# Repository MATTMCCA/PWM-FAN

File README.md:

# PWM-FAN Controller

25Khz PWM fan controller for fume extractor. Duty Range: 5%-95%, requires an external 12v supply.

Designed to control Dell Server Grade cooling fan's (*because I have one already*), or any 4-wire PC case fan.

[4-wire Fan](https://www.digikey.com/short/5pwf955c)

[Another Fan](https://www.newegg.com/p/1YF-00B0-00V81)

[Overkill Fan **2Amps**](https://www.amazon.com/Wathai-5300rpm-Airflow-Brushless-Cooling/dp/B07SGWNV5J)

## Parts-List
[DigiCart](https://www.digikey.com/short/1bbnzr3q)

___
## Notes

Some ```things``` that have caused concern are as follows,

- The Datasheet states the min/max rpm of the fan during pwm operation, ```0 rpm - 4800 rpm```. However, it also implies that the fan will never reach 0 rpm. So what exactly is the minimum speed achievable?
- I didn't add a power switch or pads for an off-board switch :rage1: . Guess ill just unplug it when I want it off? or wire a switch in series with the fan +12v wire? (**which should be rated for 2A**).
- Why do all fan controllers on amazon use high side switching instead of the actual pwm control cooked into the fan assembly? [Note the huge heat sink](https://www.amazon.com/LEDMOMO-1203BB-Controller-Adjustable-Reversible/dp/B07BLWXXQC)
- *R7 doesn't need to be populated, I checked. The fan still works with no tachometer pull-up. I thought maybe it had current sensing or something weird going on.*
- Why didn't I just buy [!!that!!](https://www.amazon.com/Wathai-Controller-Receiver-Playstation-Component/dp/B07VYGQPCZ) :rage1: *....I already sent the board to fab and bought the parts...*
---
### Fan Info

So I guess the fan *I* have is a dell model *6D237*, which has been surpassed by the *8W977*. Which might also be the *5E169*?

 I'm 78% confidant the fan linked above is almost identical, ergo, the datasheet should be a great reference for *my* fan.

### Pinout *[6D237]*
| +12 |   GND |   PWN |  SENSE |
|-----|-------|-------|--------|
| RED | BLACK | GREEN | YELLOW |

I have no idea how old the **6D237** is, google can't find it..... Still works though, so I'm a happy camper.

# Update
Boards came today, everything turned out great. Fan spins, speed is adjustable.

- I did notice, the resistors used to control min and max values from the pot arnt quite right. The min setting looks to be about 5% duty, max is still 100% duty, not 95% like projected. I'm not spinning another revision, so ill have to live with it. *The boards could be reworked, I may do that in the future*.

- I may also add an activated charcoal filter, affixed with zip ties... because... *Function Over Form*...?

---

### Board Measurements 

|   | Vcc | 5%  | 95% |
|---|---|---|---|
|Target|12.00 V|140 mV|890 mv|
|Actual| 12.31 V| 137.1 mV | 920 mV |

*After look at the potentiometer tolerance... of 20%!!!... this kinda make since. I should have picked something with a tighter tolerance, oh well, lesson learned. Functionally everything still works.*

Out of circuit one pot measured `5.30k`, in circuit the other pot measured `5.25k`.

Also, turning the knob to the right lowers the duty, turning it to the left raises the duty. I don't like it, it feels backwards (see note in schematic). I think I wired the pot backwards... so that's fun, Murphy's first law at work.

On a whim, I shorted R6. when I did that the fan kept spinning, this tells me that the fan has a min RPM that is impossible to override by driving the PWM pin to ground (as mentioned above). So it looks like there is no way to turn the fan completely off via PWM, I assume this is a safety feature, seeing as how it is a cooling fan?

---

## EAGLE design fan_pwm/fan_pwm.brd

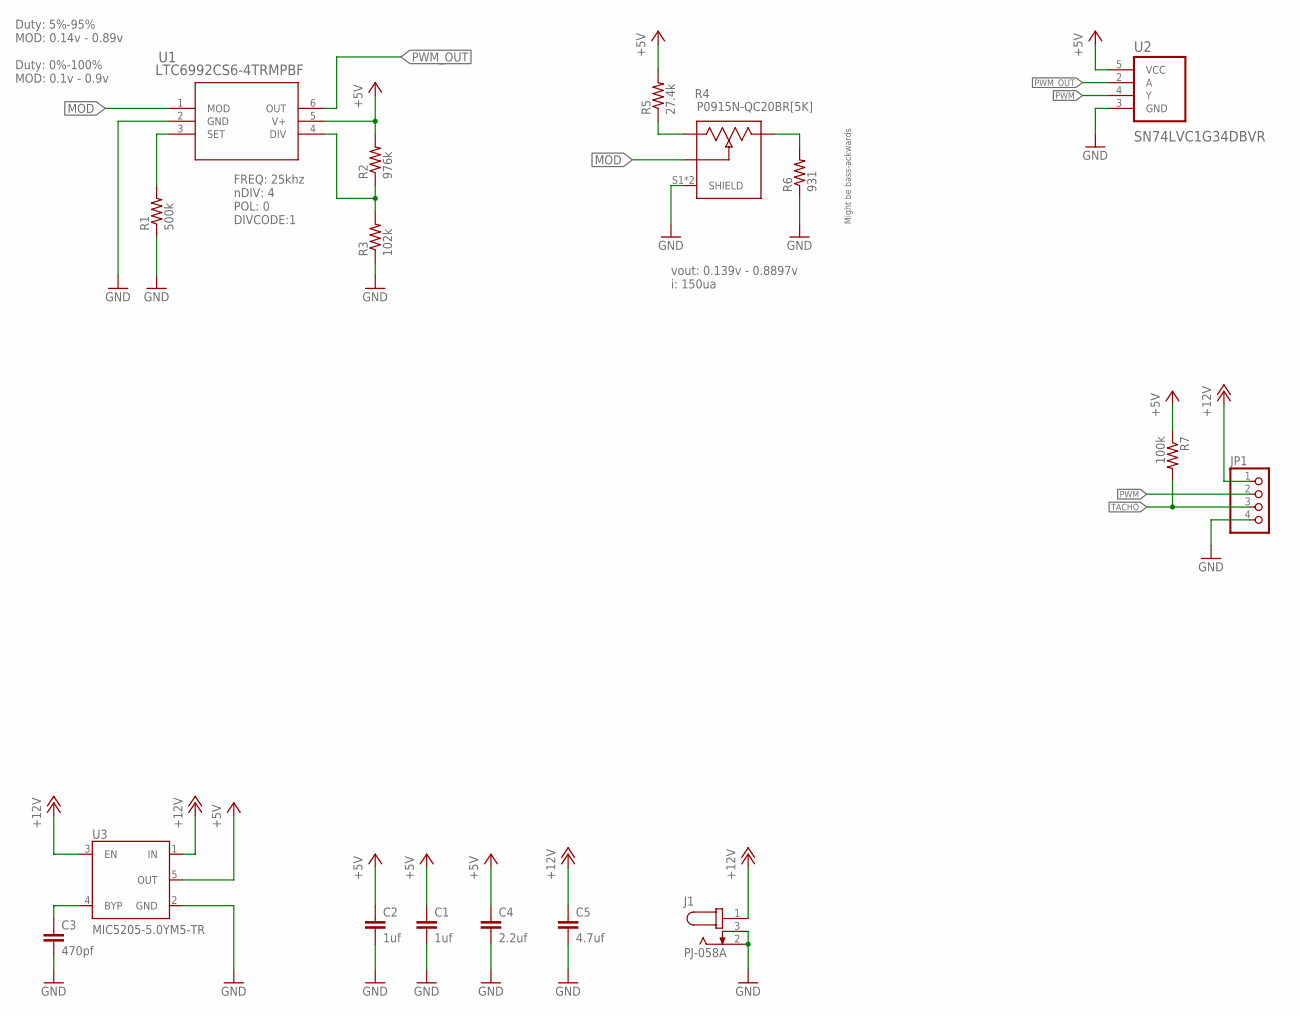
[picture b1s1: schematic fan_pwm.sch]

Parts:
C1, C2: 1uf; C0805
C3: 470pf; C0805
C4: 2.2uf; C0805
C5: 4.7uf; C0805
J1: PJ-058A; CUI_PJ-058A
JP1: PINHD-1X4; 1X04
R1: 500k; R0805
R2: 976k; R0805
R3: 102k; R0805
R4: P0915N-QC20BR[5K]; TRIM_P0915N-QC20BR5K
R5: 27.4k; R0805
R6: 931; R0805
R7: 100k; R0805
U1: LTC6992CS6-4TRMPBF; TSOT-23_S6_LIT-M
U2: SN74LVC1G34DBVR; SOT95P280X145-5N
U3: MIC5205-5.0YM5-TR; SOT95P280X145-5N

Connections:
+5V: C1.1, C2.1, C4.1, R2.2, R5.2, R7.1, U1.5 (V+), U2.5 (VCC), U3.5 (OUT)
+12V: C5.1, J1.1, JP1.1, U3.1 (IN), U3.3 (EN)
GND: C1.2, C2.2, C3.2, C4.2, C5.2, J1.2, J1.3, JP1.4, R1.1, R3.1, R4.S1 (SHIELD), R4.S2 (SHIELD), R6.1, U1.2 (GND), U2.3 (GND), U3.2 (GND)
MOD: R4.2, U1.1 (MOD)
unnamed: R1.2, U1.3 (SET)
unnamed: R4.1, R5.1
unnamed: R2.1, R3.2, U1.4 (DIV)
unnamed: R4.3, R6.2
unnamed: C3.1, U3.4 (BYP)
PWM: JP1.2, U2.4 (Y)
PWM_OUT: U1.6 (OUT), U2.2 (A)
TACHO: JP1.3, R7.2

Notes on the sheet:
FREQ: 25khz nDIV: 4 POL: 0 DIVCODE:1
Duty: 5%-95% MOD: 0.14v - 0.89v Duty: 0%-100% MOD: 0.1v - 0.9v
vout: 0.139v - 0.8897v i: 150ua
Might be bass-ackwards

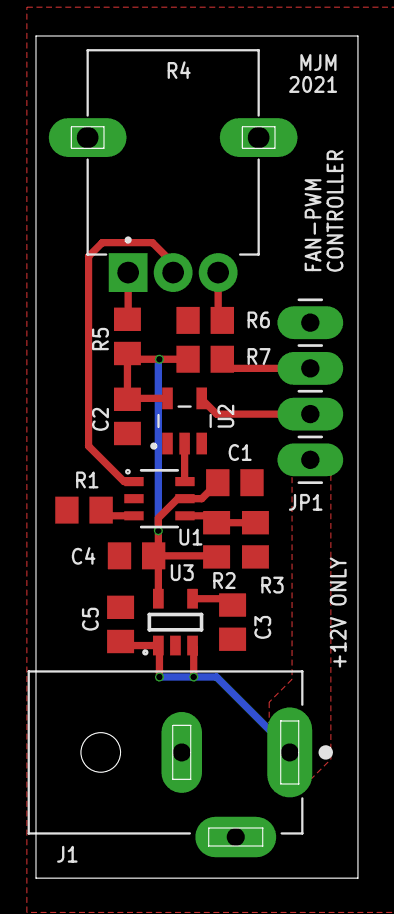
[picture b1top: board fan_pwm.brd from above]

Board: 2 copper layers, 17.9 x 46.8 mm, 17 parts (0 on the bottom side), 12 nets.

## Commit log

2021-08-29 populate
2021-08-29 tacho pullup
2021-09-06 pics

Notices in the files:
parts and their libraries:
COPYRIGHT: Copyright (C) 2021 Ultra Librarian. All rights reserved.
